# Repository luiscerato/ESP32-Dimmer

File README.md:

# ESP32-Dimmer
 Dimmer de 10 canales para AC basado en ESP32.

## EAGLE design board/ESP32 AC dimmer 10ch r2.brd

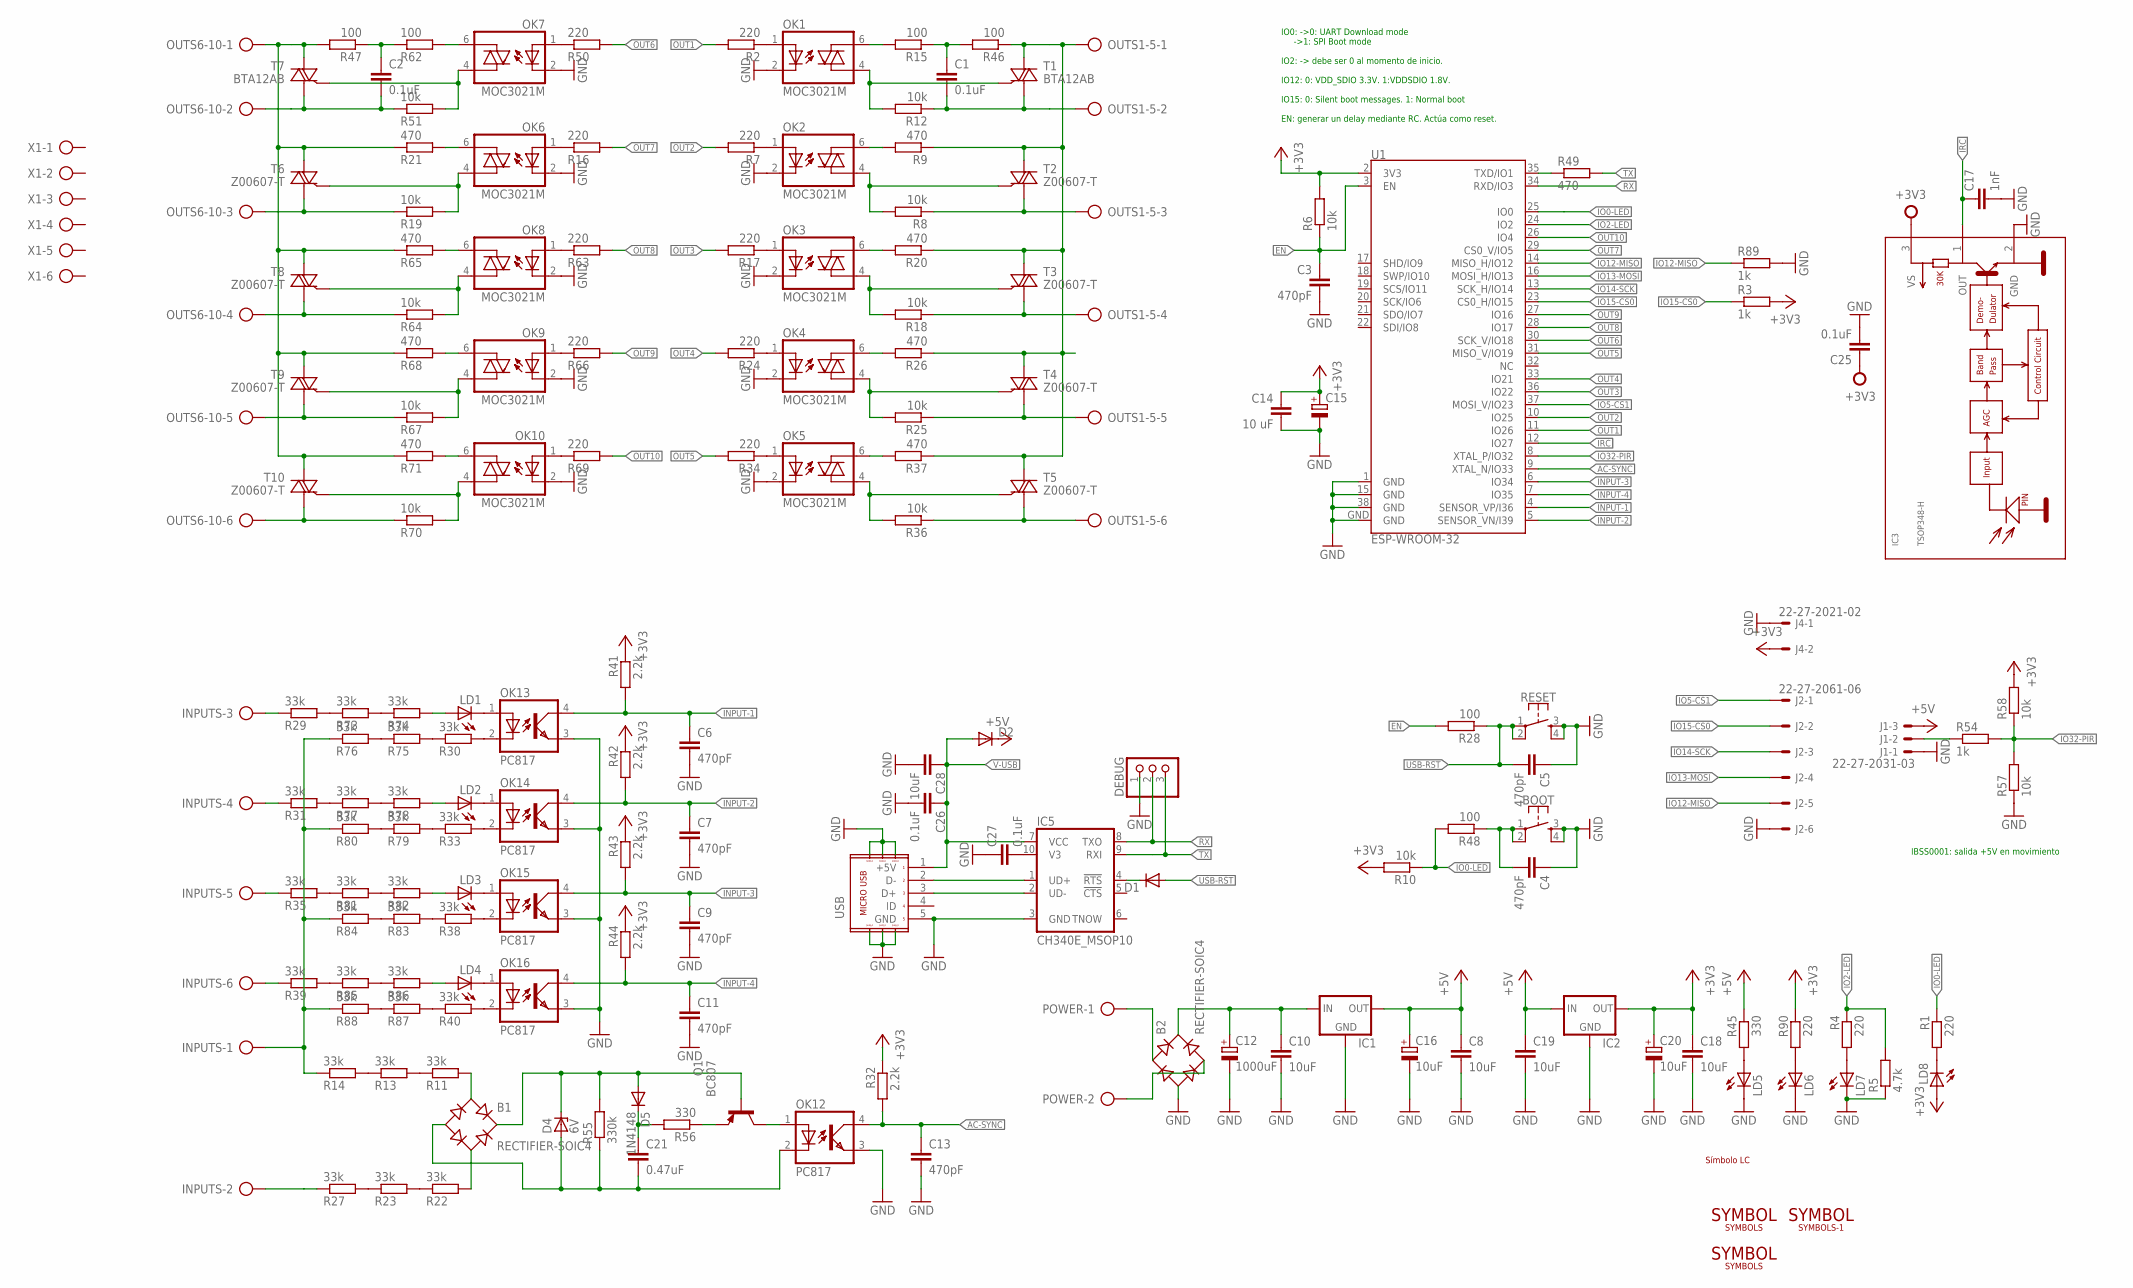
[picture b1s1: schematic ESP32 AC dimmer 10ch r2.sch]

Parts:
B1, B2: RECTIFIER-SOIC4; SOIC4
BOOT: MOMENTARY-SWITCH-SPST-2-SMD-4.6X2.8MM; TACTILE_SWITCH_SMD_4.6X2.8MM
C1, C2: 0.1uF; C075-042X103
C3, C4, C5, C6, C7, C9, C11, C13: 470pF; C0603
C8, C10, C18, C19: 10uF; C0805
C12: 1000uF; E3,5-8
C14: 10 uF; C0805
C15: CPOL-EUSMCA; SMC_A
C16, C20: 10uF; SMC_A
C17: 1nF; C0603
C21: 0.47uF; C0805
C25, C26, C27: 0.1uF; C0603
C28: 10uF; RCL_C0805
D1, D2: DIODE-SOD323-R; SOD323-R
D4: 6V; SOD80C
D5: 1N4148; MINIMELF
DEBUG: PINHD-1X3; 1X03
IC1, IC2: LM1117; SOT223
IC3: TSOP348-H; TSOP348H
IC5: CH340E_MSOP10; MSOP10
INPUTS: AK500/6
J1: 22-27-2031-03; 6410-03
J2: 22-27-2061-06; 6410-06
J4: 22-27-2021-02; 6410-02
LD1, LD2, LD3, LD4, LD5, LD6, LD7, LD8: LEDCHIPLED_0805; CHIPLED_0805
OK1, OK2, OK3, OK4, OK5, OK6, OK7, OK8, OK9, OK10: MOC3021M; DIL06
OK12, OK13, OK14, OK15, OK16: PC817; DIL04
OUTS1-5, OUTS6-10: AK500/6
POWER: AK500/2
Q1: BC807; SOT23-BEC
R1, R2, R4, R7, R16, R17, R24, R34, R50, R63, R66, R69, R90: 220; R0603
R3, R54, R89: 1k; R0603
R5: 4.7k; R0603
R6, R10, R57, R58: 10k; R0603
R8, R12, R18, R19, R25, R36, R51, R64, R67, R70: 10k; 0204/5
R9, R20, R21, R26, R37, R65, R68, R71: 470; 0204/5
R11, R13, R14, R22, R23, R27, R29, R30, R31, R33, R35, R38, R39, R40, R73, R74, R75, R76, R77, R78, R79, R80, R81, R82, R83, R84, R85, R86, R87, R88: 33k; R0805
R15, R62: 100; 0204/5
R28, R48: 100; R0603
R32, R41, R42, R43, R44: 2.2k; R0603
R45: 330; R0603
R46, R47: 100; 0204/7
R49: 470; R0603
R55: 330k; R0805
R56: 330; R0805
RESET: MOMENTARY-SWITCH-SPST-2-SMD-4.6X2.8MM; TACTILE_SWITCH_SMD_4.6X2.8MM
SYM1: LC-3.81; LC_3.81MM
T1, T7: BTA12AB; TO220DS
T2, T3, T4, T5, T6, T8, T9, T10: Z00607-T; TO92-A1GA2
U1: ESP-WROOM-32
U$1, U$2: SYMBOLS; WIFI_SYM
U$3: SYMBOLS-1; WIFI-SYM2
USB: MICROUSB-LP; MICROUSB-4PIN-LONGPIN
X1: AK300/6

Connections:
+3V3: C14.1, C15.+, C18.1, C20.+, C25.1, IC2.2 (OUT), IC3.3 (VS), J4.2, LD8.A, R3.2, R6.2, R10.2, R32.1, R41.1, R42.1, R43.1, R44.1, R58.2, R90.1, U1.2 (3V3)
+5V: C8.1, C16.+, C19.1, D2.C, IC1.2 (OUT), IC2.3 (IN), J1.3, R45.1
AC-SYNC: C13.1, OK12.4 (COL), R32.2, U1.9 (XTAL_N/IO33)
EN: C3.1, R6.1, R28.2, U1.3 (EN)
FASE: OUTS6-10.1, R21.1, R47.2, R65.1, R68.1, R71.1, T6.A2, T7.A2, T8.A2, T9.A2, T10.A2
FASE1: OUTS1-5.1, R9.1, R20.1, R26.1, R37.1, R46.1, T1.A2, T2.A2, T3.A2, T4.A2, T5.A2
GND: B2.-, BOOT.3, BOOT.4, C3.2, C4.1, C5.1, C6.2, C7.2, C8.2, C9.2, C10.2, C11.2, C12.-, C13.2, C14.2, C15.-, C16.-, C17.2, C18.2, C19.2, C20.-, C25.2, C26.2, C27.1, C28.2, DEBUG.1, IC1.1 (GND), IC2.1 (GND), IC3.2 (GND), IC5.3 (GND), J1.1, J2.6, J4.1, LD5.C, LD6.C, LD7.C, OK1.2 (C), OK2.2 (C), OK3.2 (C), OK4.2 (C), OK5.2 (C), OK6.2 (C), OK7.2 (C), OK8.2 (C), OK9.2 (C), OK10.2 (C), OK12.3 (EMIT), OK13.3 (EMIT), OK14.3 (EMIT), OK15.3 (EMIT), OK16.3 (EMIT), R5.1, R57.1, R89.2, RESET.3, RESET.4, U1.1 (GND), U1.15 (GND), U1.38 (GND), U1.GND, USB.5 (GND), USB.P1, USB.P2, USB.P3, USB.P4, USB.P5, USB.P6
INPUT-1: C6.1, OK13.4 (COL), R41.2, U1.4 (SENSOR_VP/I36)
INPUT-2: C7.1, OK14.4 (COL), R42.2, U1.5 (SENSOR_VN/I39)
INPUT-3: C9.1, OK15.4 (COL), R43.2, U1.6 (IO34)
INPUT-4: C11.1, OK16.4 (COL), R44.2, U1.7 (IO35)
IO0-LED: R1.1, R10.1, R48.2, U1.25 (IO0)
IO2-LED: R4.1, R5.2, U1.24 (IO2)
IO5-CS1: J2.1, U1.37 (MOSI_V/IO23)
IO12-MISO: J2.5, R89.1, U1.14 (MISO_H/IO12)
IO13-MOSI: J2.4, U1.16 (MOSI_H/IO13)
IO14-SCK: J2.3, U1.13 (SCK_H/IO14)
IO15-CS0: J2.2, R3.1, U1.23 (CS0_H/IO15)
IO32-PIR: R54.2, R57.2, R58.1, U1.8 (XTAL_P/IO32)
IRC: C17.1, IC3.1 (OUT), U1.12 (IO27)
unnamed: OK7.1 (A), R50.1
unnamed: OK8.1 (A), R63.1
unnamed: OK9.1 (A), R66.1
unnamed: OK10.1 (A), R69.1
unnamed: OK1.4 (A1), R12.2, T1.G
unnamed: OK1.6 (A2), R15.2
unnamed: D1.C, IC5.4 (!RTS)
unnamed: LD8.C, R1.2
unnamed: R49.1, U1.35 (TXD/IO1)
unnamed: OUTS1-5.6, R36.1, T5.A1
unnamed: OK2.4 (A1), R8.2, T2.G
unnamed: OK2.6 (A2), R9.2
unnamed: OUTS6-10.3, R19.1, T6.A1
unnamed: C2.2, OUTS6-10.2, R51.1, T7.A1
unnamed: OK6.4 (A1), R19.2, T6.G
unnamed: OK6.6 (A2), R21.2
unnamed: OK3.4 (A1), R18.2, T3.G
unnamed: OUTS6-10.4, R64.1, T8.A1
unnamed: OK3.6 (A2), R20.2
unnamed: OUTS6-10.5, R67.1, T9.A1
unnamed: OUTS6-10.6, R70.1, T10.A1
unnamed: B2.+, C10.1, C12.+, IC1.3 (IN)
unnamed: LD6.A, R90.2
unnamed: LD7.A, R4.2
unnamed: OK7.4 (A1), R51.2, T7.G
unnamed: OK7.6 (A2), R62.2
unnamed: OK4.4 (A1), R25.2, T4.G
unnamed: OK4.6 (A2), R26.2
unnamed: OK1.1 (A), R2.1
unnamed: R11.1, R13.2
unnamed: OK5.4 (A1), R36.2, T5.G
unnamed: OK5.6 (A2), R37.2
unnamed: R13.1, R14.2
unnamed: R22.1, R23.2
unnamed: R23.1, R27.2
unnamed: BOOT.1, BOOT.2, C4.2, R48.1
unnamed: B2.AC1, POWER.1
unnamed: OK2.1 (A), R7.1
unnamed: OK3.1 (A), R17.1
unnamed: OK4.1 (A), R24.1
unnamed: OK8.4 (A1), R64.2, T8.G
unnamed: OK8.6 (A2), R65.2
unnamed: OK9.4 (A1), R67.2, T9.G
unnamed: B1.+, D4.C, D5.A, Q1.B, R55.2
unnamed: OK12.1 (A), Q1.C
unnamed: OK9.6 (A2), R68.2
unnamed: OK10.4 (A1), R70.2, T10.G
unnamed: OK10.6 (A2), R71.2
unnamed: OK5.1 (A), R34.1
unnamed: OK6.1 (A), R16.1
unnamed: B2.AC2, POWER.2
unnamed: LD1.C, OK13.1 (A)
unnamed: OK13.2 (C), R30.2
unnamed: Q1.E, R56.1
unnamed: LD1.A, R74.2
unnamed: C21.1, D5.C, R56.2
unnamed: OK14.2 (C), R33.2
unnamed: INPUTS.2, R27.1
unnamed: B1.AC2, R22.2
unnamed: LD2.C, OK14.1 (A)
unnamed: B1.-, C21.2, D4.A, OK12.2 (C), R55.1
unnamed: OK15.2 (C), R38.2
unnamed: LD2.A, R78.2
unnamed: OK16.2 (C), R40.2
unnamed: INPUTS.3, R29.1
unnamed: INPUTS.4, R31.1
unnamed: INPUTS.5, R35.1
unnamed: INPUTS.1, R14.1, R76.1, R80.1, R84.1, R88.1
unnamed: INPUTS.6, R39.1
unnamed: LD3.C, OK15.1 (A)
unnamed: LD3.A, R82.2
unnamed: LD4.C, OK16.1 (A)
unnamed: LD4.A, R86.2
unnamed: LD5.A, R45.2
unnamed: C1.1, R15.1, R46.2
unnamed: C2.1, R47.1, R62.1
unnamed: B1.AC1, R11.2
unnamed: J1.2, R54.1
unnamed: R29.2, R73.1
unnamed: R73.2, R74.1
unnamed: R30.1, R75.2
unnamed: R75.1, R76.2
unnamed: R31.2, R77.1
unnamed: R77.2, R78.1
unnamed: R33.1, R79.2
unnamed: R79.1, R80.2
unnamed: R35.2, R81.1
unnamed: R81.2, R82.1
unnamed: R38.1, R83.2
unnamed: R83.1, R84.2
unnamed: R39.2, R85.1
unnamed: R85.2, R86.1
unnamed: R40.1, R87.2
unnamed: R87.1, R88.2
unnamed: IC5.1 (UD+), USB.2 (D-)
unnamed: IC5.2 (UD-), USB.3 (D+)
unnamed: C1.2, OUTS1-5.2, R12.1, T1.A1
unnamed: OUTS1-5.3, R8.1, T2.A1
unnamed: C27.2, IC5.10 (V3)
unnamed: OUTS1-5.4, R18.1, T3.A1
unnamed: OUTS1-5.5, R25.1, T4.A1
OUT1: R2.2, U1.11 (IO26)
OUT2: R7.2, U1.10 (IO25)
OUT3: R17.2, U1.36 (IO22)
OUT4: R24.2, U1.33 (IO21)
OUT5: R34.2, U1.31 (MISO_V/IO19)
OUT6: R50.2, U1.30 (SCK_V/IO18)
OUT7: R16.2, U1.29 (CS0_V/IO5)
OUT8: R63.2, U1.28 (IO17)
OUT9: R66.2, U1.27 (IO16)
OUT10: R69.2, U1.26 (IO4)
RX: DEBUG.2, IC5.8 (TXO), U1.34 (RXD/IO3)
TX: DEBUG.3, IC5.9 (RXI), R49.2
USB-RST: C5.2, D1.A, R28.1, RESET.1, RESET.2
V-USB: C26.1, C28.1, D2.A, IC5.7 (VCC), USB.1 (+5V)

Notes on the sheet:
IO0: ->0: UART Download mode ->1: SPI Boot mode IO2: -> debe ser 0 al momento de inicio. IO12: 0: VDD_SDIO 3.3V. 1:VDDSDIO 1.8V. IO15: 0: Silent boot messages. 1: Normal boot EN: generar un delay mediante RC. Actúa como reset.
IBSS0001: salida +5V en movimiento

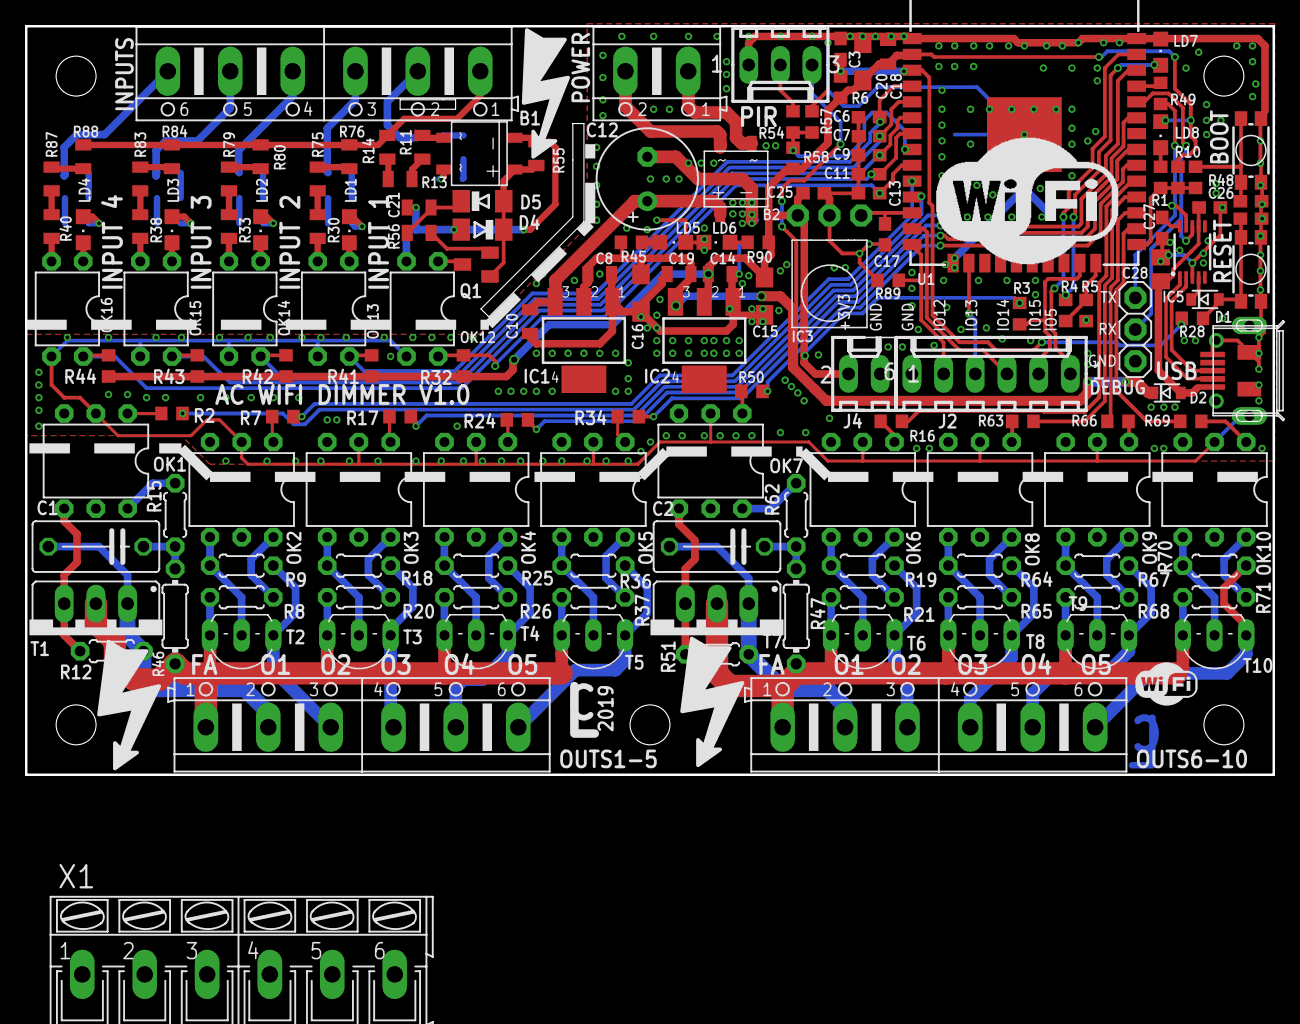
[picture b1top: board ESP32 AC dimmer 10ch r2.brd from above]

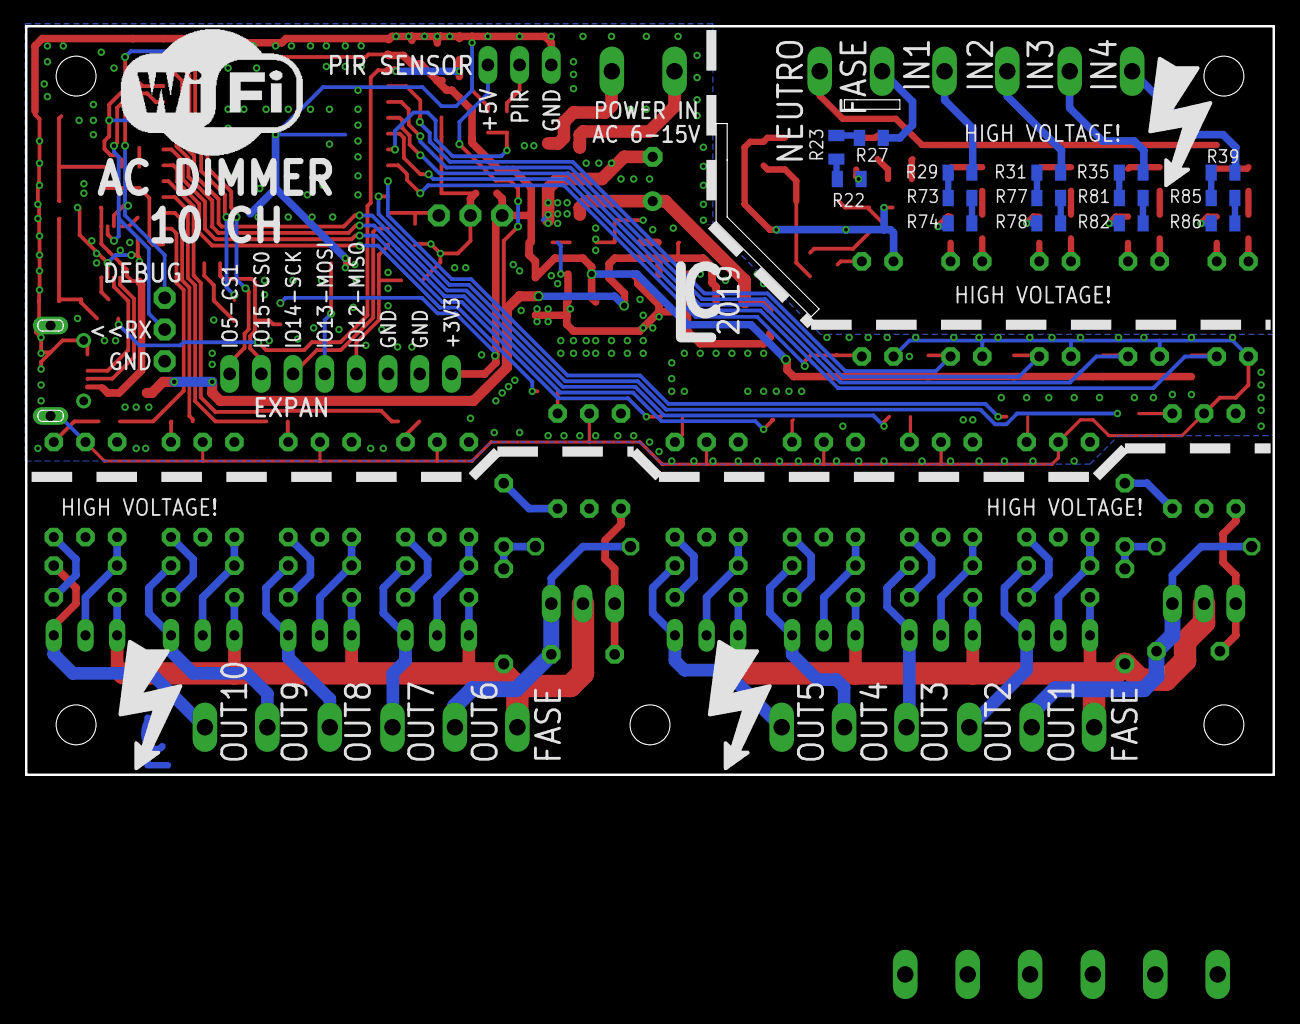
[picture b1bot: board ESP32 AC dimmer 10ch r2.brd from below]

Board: 2 copper layers, 100.0 x 60.0 mm, 170 parts (17 on the bottom side), 135 nets.

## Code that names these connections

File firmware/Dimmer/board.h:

#ifndef BOARD_AC_DIMMER_10CH
#define BOARD_AC_DIMMER_10CH
#include "arduino.h"

class board {
#define OUT1 26
#define OUT2 25
#define OUT3 22
#define OUT4 21
#define OUT5 19
#define OUT6 18
#define OUT7 5
#define OUT8 17
#define OUT9 16
#define OUT10 4

#define INPUT1 36
#define INPUT2 39
#define INPUT3 34
#define INPUT4 35

#define INPUT_ZCD 33
#define INPUT_PIR 32
#define INPUT_IRC 27

#define LED1 2
#define LED2 0

#define IO5 23
#define IO12 12
#define IO13 13
#define IO14 14
#define IO15 15

public:
	const char *BOARD_NAME;
	const uint8_t *Pins_Outputs;
	const uint8_t *Pins_Inputs;

	void begin();

	void LED1_Toggle();

	void LED1_Off();

	void LED1_On();

	bool LED1_GetState();

	void LED2_Toggle();

	void LED2_Off();

	void LED2_On();

	bool LED2_GetState();

};

extern board Board;
extern const uint8_t Pins_Outs[];
extern const uint8_t Pins_Leds[];
extern const uint8_t Pins_Input[];

#endif

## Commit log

2019-10-27 MQTT disabled
    Se desactiva cliente MQTT porque cuelga el procesador.

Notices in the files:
parts and their libraries:
SparkFun-RF: Licensing: Creative Commons ShareAlike 4.0 International - https://creativecommons.org/licenses/by-sa/4.0
